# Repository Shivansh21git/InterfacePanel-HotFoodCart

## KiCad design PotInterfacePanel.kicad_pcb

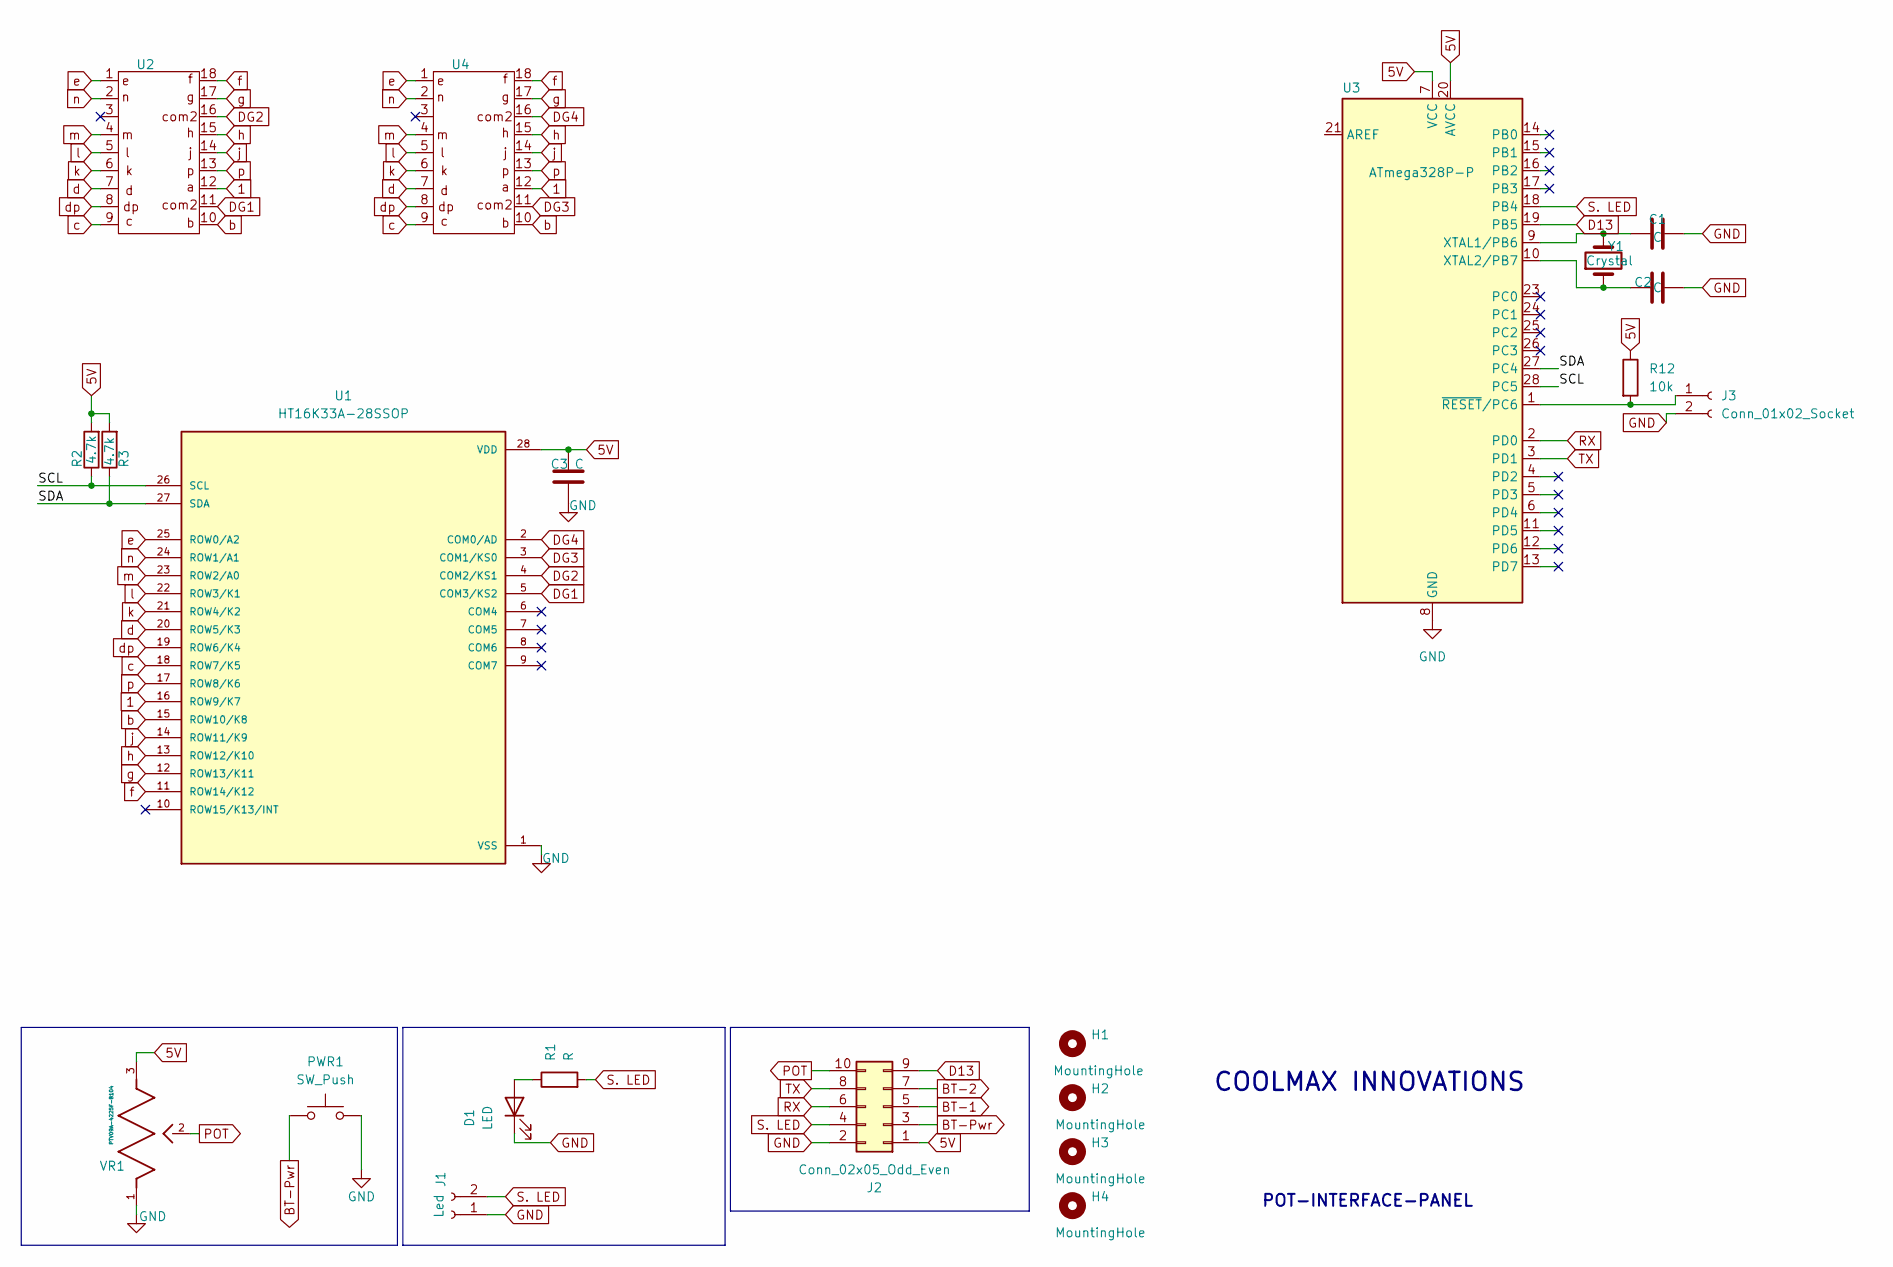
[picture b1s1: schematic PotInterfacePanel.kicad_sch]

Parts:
C1, C2, C3: C; C_Disc_D3.0mm_W1.6mm_P2.50mm
D1: LED; LED_D3.0mm
H1, H2, H3, H4: MountingHole; MountingHole_2.2mm_M2
J1: Led; JST_EH_B2B-EH-A_1x02_P2.50mm_Vertical
J2: Conn_02x05_Odd_Even; IDC-Header_2x05_P2.54mm_Vertical
J3: Conn_01x02_Socket; PinHeader_1x02_P1.27mm_Vertical
PWR1: SW_Push; SW_PUSH-12mm
R1: R; R_Axial_DIN0204_L3.6mm_D1.6mm_P5.08mm_Horizontal
R2, R3: 4.7k; R_Axial_DIN0204_L3.6mm_D1.6mm_P5.08mm_Horizontal
R12: 10k; R_Axial_DIN0204_L3.6mm_D1.6mm_P5.08mm_Horizontal
U1: HT16K33A-28SSOP; SOP63P600X175-28N; PARTREV 1.02
U2, U4: 14seg
U3: ATmega328P-P; DIP-28_W7.62mm
VR1: PTV09A-4225F-B104; PTV09; PARTNO PTV09A-4225F-B104-ND
Y1: Crystal; Crystal_HC18-U_Vertical

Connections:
1: U1.16 (ROW9/K7), U2.12, U4.12
5V: C3.2, J2.1, R2.2, R3.2, R12.1, U1.28 (VDD), U3.7 (VCC), U3.20 (AVCC), VR1.3
/SCL: R2.1, U1.26 (SCL), U3.28 (PC5)
/SDA: R3.1, U1.27 (SDA), U3.27 (PC4)
BT-1: J2.5
BT-2: J2.7
BT-Pwr: J2.3, PWR1.1
D13: J2.9, U3.19 (PB5)
DG1: U1.5 (COM3/KS2), U2.11
DG2: U1.4 (COM2/KS1), U2.16
DG3: U1.3 (COM1/KS0), U4.11
DG4: U1.2 (COM0/AD), U4.16
GND: C1.2, C2.2, C3.1, D1.1 (K), J1.1, J2.2, J3.2, PWR1.2, U1.1 (VSS), U3.8 (GND), U3.22 (GND), VR1.1
unnamed: D1.2 (A), R1.1
unnamed: J3.1, R12.2, U3.1 (~RESET/PC6)
unnamed: C1.1, U3.9 (XTAL1/PB6), Y1.2
unnamed: C2.1, U3.10 (XTAL2/PB7), Y1.1
POT: J2.10, VR1.2
RX: J2.6, U3.2 (PD0)
S. LED: J1.2, J2.4, R1.2, U3.18 (PB4)
TX: J2.8, U3.3 (PD1)
b: U1.15 (ROW10/K8), U2.10, U4.10
c: U1.18 (ROW7/K5), U2.9, U4.9
d: U1.20 (ROW5/K3), U2.7, U4.7
dp: U1.19 (ROW6/K4), U2.8, U4.8
e: U1.25 (ROW0/A2), U2.1, U4.1
f: U1.11 (ROW14/K12), U2.18, U4.18
g: U1.12 (ROW13/K11), U2.17, U4.17
h: U1.13 (ROW12/K10), U2.15, U4.15
j: U1.14 (ROW11/K9), U2.14, U4.14
k: U1.21 (ROW4/K2), U2.6, U4.6
l: U1.22 (ROW3/K1), U2.5, U4.5
m: U1.23 (ROW2/A0), U2.4, U4.4
n: U1.24 (ROW1/A1), U2.2, U4.2
p: U1.17 (ROW8/K6), U2.13, U4.13

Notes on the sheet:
POT-INTERFACE-PANEL
COOLMAX INNOVATIONS

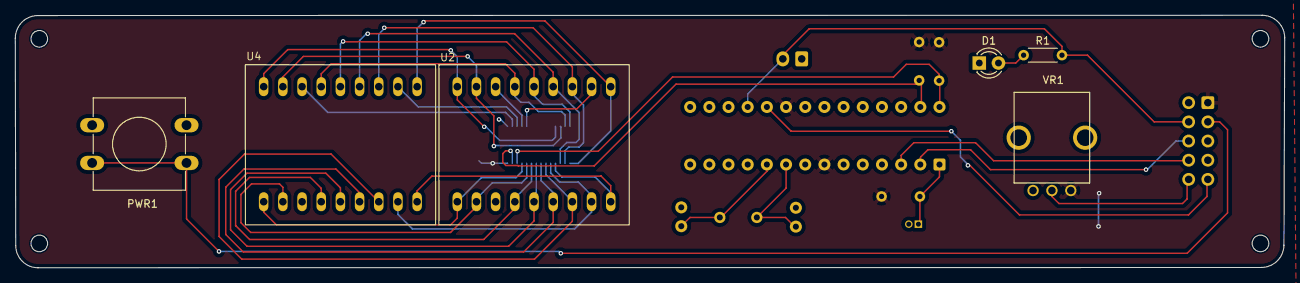
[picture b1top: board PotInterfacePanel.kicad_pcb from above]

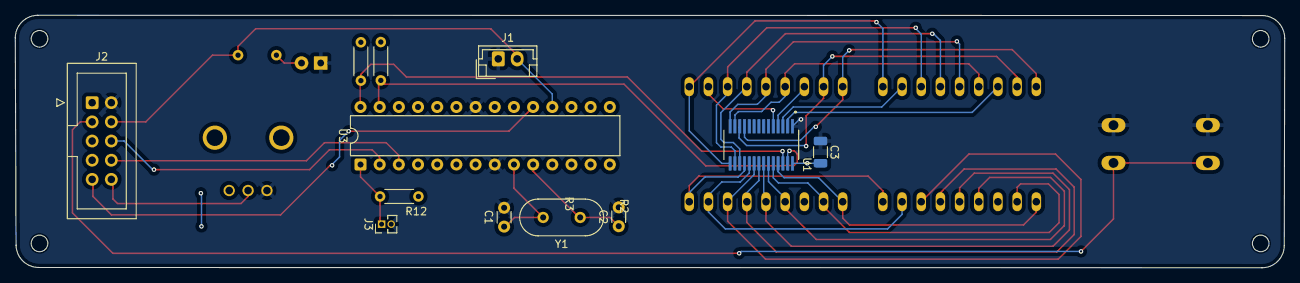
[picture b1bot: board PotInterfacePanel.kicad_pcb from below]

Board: 2 copper layers, 168.1 x 33.4 mm, 22 parts (12 on the bottom side), 33 nets.

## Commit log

2025-09-17 initial save
2025-12-04 14seg-Display with a Potentiometer Knob
2025-12-04 14seg-Display with a Potentiometer Knob remote added
2025-12-04 3dfiles
